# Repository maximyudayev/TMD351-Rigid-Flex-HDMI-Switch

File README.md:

# Rigid-Flex HDMI Switch - TI TMDS351
This HDMI switch board was built as part of my Hardware Design course at KU Leuven - Campus GroupT in academic year 2020-2021, taught by the awesome Gorik :wink:

PCB front side:

PCB back side:

Mechanical layer details:

100 Ohm differential trace width:

All the design files are under GPL3 and can be freely used for personal projects where this device can be of use.

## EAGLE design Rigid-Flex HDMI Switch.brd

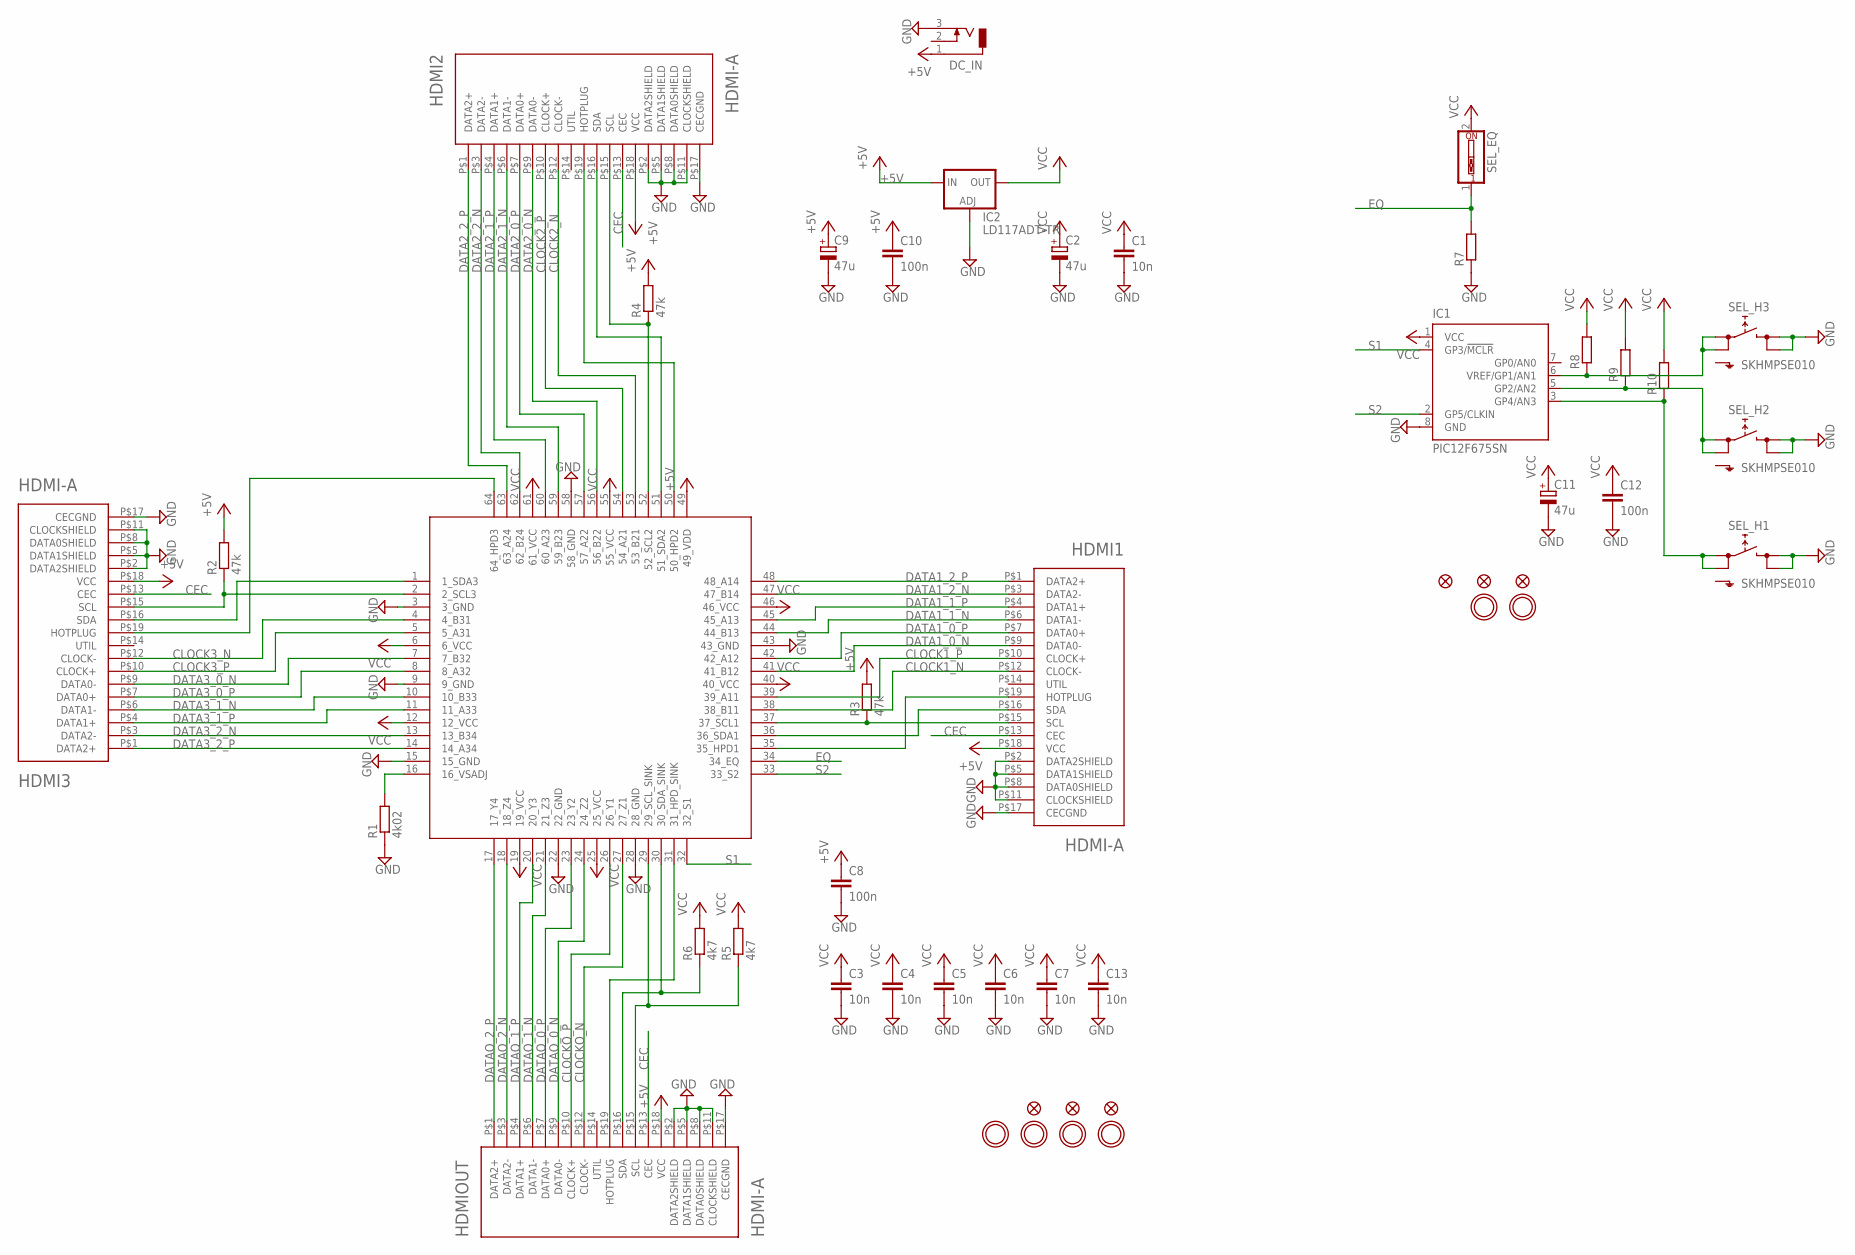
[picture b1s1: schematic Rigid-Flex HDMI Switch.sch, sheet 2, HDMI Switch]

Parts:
C1: 10n; C0402
C2, C9, C11: 47u; SMC_A
C3, C4, C5, C6, C7, C13: 10n; 0402
C8: 100n; 0402
C10, C12: 100n; C0402
DC_IN: DCJ0303
FID1, FID2, FID3, FID4, FID5, FID6: FIDUCIAL""; FIDUCIAL_1MM
HDMI1, HDMI2, HDMI3: HDMI-A; HDMI_A
HDMIOUT: HDMI-A; HDMI_A
IC1: PIC12F675SN; SO-08
IC2: LD117ADT-TR; DPACK
R1: 4k02; 0402
R2, R3, R4: 47k; 0402
R5, R6: 4k7; 0402
R7, R8, R9, R10: R-EU_R0805; R0805
SEL_EQ: SW_DIP-1; EDG-01
SEL_H1, SEL_H2, SEL_H3: SKHMPSE010; SKHMPXE010
U1: TMDS351TQFP64; QFP50P1200X1200X120-64
U$1, U$2, U$31, U$32, U$33, U$34: MOUNTINGHOLE3.0; MOUNTINGHOLE_3.0_PLATED

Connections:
+5V: C8.1, C9.+, C10.1, DC_IN.1, HDMI1.P$18 (VCC), HDMI2.P$18 (VCC), HDMI3.P$18 (VCC), HDMIOUT.P$18 (VCC), IC2.3 (IN), R2.2, R3.2, R4.2, U1.49 (49_VDD)
CEC: HDMI1.P$13 (CEC), HDMI2.P$13 (CEC), HDMI3.P$13 (CEC), HDMIOUT.P$13 (CEC)
CLOCK1_N: HDMI1.P$12 (CLOCK-), U1.38 (38_B11)
CLOCK1_P: HDMI1.P$10 (CLOCK+), U1.39 (39_A11)
CLOCK2_N: HDMI2.P$12 (CLOCK-), U1.53 (53_B21)
CLOCK2_P: HDMI2.P$10 (CLOCK+), U1.54 (54_A21)
CLOCK3_N: HDMI3.P$12 (CLOCK-), U1.4 (4_B31)
CLOCK3_P: HDMI3.P$10 (CLOCK+), U1.5 (5_A31)
CLOCKO_N: HDMIOUT.P$12 (CLOCK-), U1.27 (27_Z1)
CLOCKO_P: HDMIOUT.P$10 (CLOCK+), U1.26 (26_Y1)
DATA1_0_N: HDMI1.P$9 (DATA0-), U1.41 (41_B12)
DATA1_0_P: HDMI1.P$7 (DATA0+), U1.42 (42_A12)
DATA1_1_N: HDMI1.P$6 (DATA1-), U1.44 (44_B13)
DATA1_1_P: HDMI1.P$4 (DATA1+), U1.45 (45_A13)
DATA1_2_N: HDMI1.P$3 (DATA2-), U1.47 (47_B14)
DATA1_2_P: HDMI1.P$1 (DATA2+), U1.48 (48_A14)
DATA2_0_N: HDMI2.P$9 (DATA0-), U1.56 (56_B22)
DATA2_0_P: HDMI2.P$7 (DATA0+), U1.57 (57_A22)
DATA2_1_N: HDMI2.P$6 (DATA1-), U1.59 (59_B23)
DATA2_1_P: HDMI2.P$4 (DATA1+), U1.60 (60_A23)
DATA2_2_N: HDMI2.P$3 (DATA2-), U1.62 (62_B24)
DATA2_2_P: HDMI2.P$1 (DATA2+), U1.63 (63_A24)
DATA3_0_N: HDMI3.P$9 (DATA0-), U1.7 (7_B32)
DATA3_0_P: HDMI3.P$7 (DATA0+), U1.8 (8_A32)
DATA3_1_N: HDMI3.P$6 (DATA1-), U1.10 (10_B33)
DATA3_1_P: HDMI3.P$4 (DATA1+), U1.11 (11_A33)
DATA3_2_N: HDMI3.P$3 (DATA2-), U1.13 (13_B34)
DATA3_2_P: HDMI3.P$1 (DATA2+), U1.14 (14_A34)
DATAO_0_N: HDMIOUT.P$9 (DATA0-), U1.24 (24_Z2)
DATAO_0_P: HDMIOUT.P$7 (DATA0+), U1.23 (23_Y2)
DATAO_1_N: HDMIOUT.P$6 (DATA1-), U1.21 (21_Z3)
DATAO_1_P: HDMIOUT.P$4 (DATA1+), U1.20 (20_Y3)
DATAO_2_N: HDMIOUT.P$3 (DATA2-), U1.18 (18_Z4)
DATAO_2_P: HDMIOUT.P$1 (DATA2+), U1.17 (17_Y4)
EQ: R7.2, SEL_EQ.1, U1.34 (34_EQ)
GND: C1.2, C2.-, C3.2, C4.2, C5.2, C6.2, C7.2, C8.2, C9.-, C10.2, C11.-, C12.2, C13.2, DC_IN.3, HDMI1.P$2 (DATA2SHIELD), HDMI1.P$5 (DATA1SHIELD), HDMI1.P$8 (DATA0SHIELD), HDMI1.P$11 (CLOCKSHIELD), HDMI1.P$17 (CECGND), HDMI2.P$2 (DATA2SHIELD), HDMI2.P$5 (DATA1SHIELD), HDMI2.P$8 (DATA0SHIELD), HDMI2.P$11 (CLOCKSHIELD), HDMI2.P$17 (CECGND), HDMI3.P$2 (DATA2SHIELD), HDMI3.P$5 (DATA1SHIELD), HDMI3.P$8 (DATA0SHIELD), HDMI3.P$11 (CLOCKSHIELD), HDMI3.P$17 (CECGND), HDMIOUT.P$2 (DATA2SHIELD), HDMIOUT.P$5 (DATA1SHIELD), HDMIOUT.P$8 (DATA0SHIELD), HDMIOUT.P$11 (CLOCKSHIELD), HDMIOUT.P$17 (CECGND), IC1.8 (GND), IC2.1 (ADJ), R1.1, R7.1, SEL_H1.3 (2.1), SEL_H1.4 (2.2), SEL_H2.3 (2.1), SEL_H2.4 (2.2), SEL_H3.3 (2.1), SEL_H3.4 (2.2), U1.3 (3_GND), U1.9 (9_GND), U1.15 (15_GND), U1.22 (22_GND), U1.28 (28_GND), U1.43 (43_GND), U1.58 (58_GND)
unnamed: HDMI3.P$19 (HOTPLUG), U1.64 (64_HPD3)
unnamed: HDMI2.P$19 (HOTPLUG), U1.50 (50_HPD2)
unnamed: HDMI1.P$19 (HOTPLUG), U1.35 (35_HPD1)
unnamed: HDMIOUT.P$19 (HOTPLUG), U1.31 (31_HPD_SINK)
unnamed: HDMI3.P$16 (SDA), U1.1 (1_SDA3)
unnamed: HDMI3.P$15 (SCL), R2.1, U1.2 (2_SCL3)
unnamed: HDMI2.P$16 (SDA), U1.51 (51_SDA2)
unnamed: HDMI2.P$15 (SCL), R4.1, U1.52 (52_SCL2)
unnamed: HDMI1.P$15 (SCL), R3.1, U1.37 (37_SCL1)
unnamed: HDMI1.P$16 (SDA), U1.36 (36_SDA1)
unnamed: HDMIOUT.P$16 (SDA), R6.1, U1.30 (30_SDA_SINK)
unnamed: HDMIOUT.P$15 (SCL), R5.1, U1.29 (29_SCL_SINK)
unnamed: R1.2, U1.16 (16_VSADJ)
unnamed: IC1.6 (VREF/GP1/AN1), R8.1, SEL_H3.1 (1.1), SEL_H3.2 (1.2)
unnamed: IC1.5 (GP2/AN2), R9.1, SEL_H2.1 (1.1), SEL_H2.2 (1.2)
unnamed: IC1.3 (GP4/AN3), R10.1, SEL_H1.1 (1.1), SEL_H1.2 (1.2)
S1: IC1.4 (GP3/!MCLR), U1.32 (32_S1)
S2: IC1.2 (GP5/CLKIN), U1.33 (33_S2)
VCC: C1.1, C2.+, C3.1, C4.1, C5.1, C6.1, C7.1, C11.+, C12.1, C13.1, IC1.1 (VCC), IC2.4 (OUT), R5.2, R6.2, R8.2, R9.2, R10.2, SEL_EQ.2, U1.6 (6_VCC), U1.12 (12_VCC), U1.19 (19_VCC), U1.25 (25_VCC), U1.40 (40_VCC), U1.46 (46_VCC), U1.55 (55_VCC), U1.61 (61_VCC)

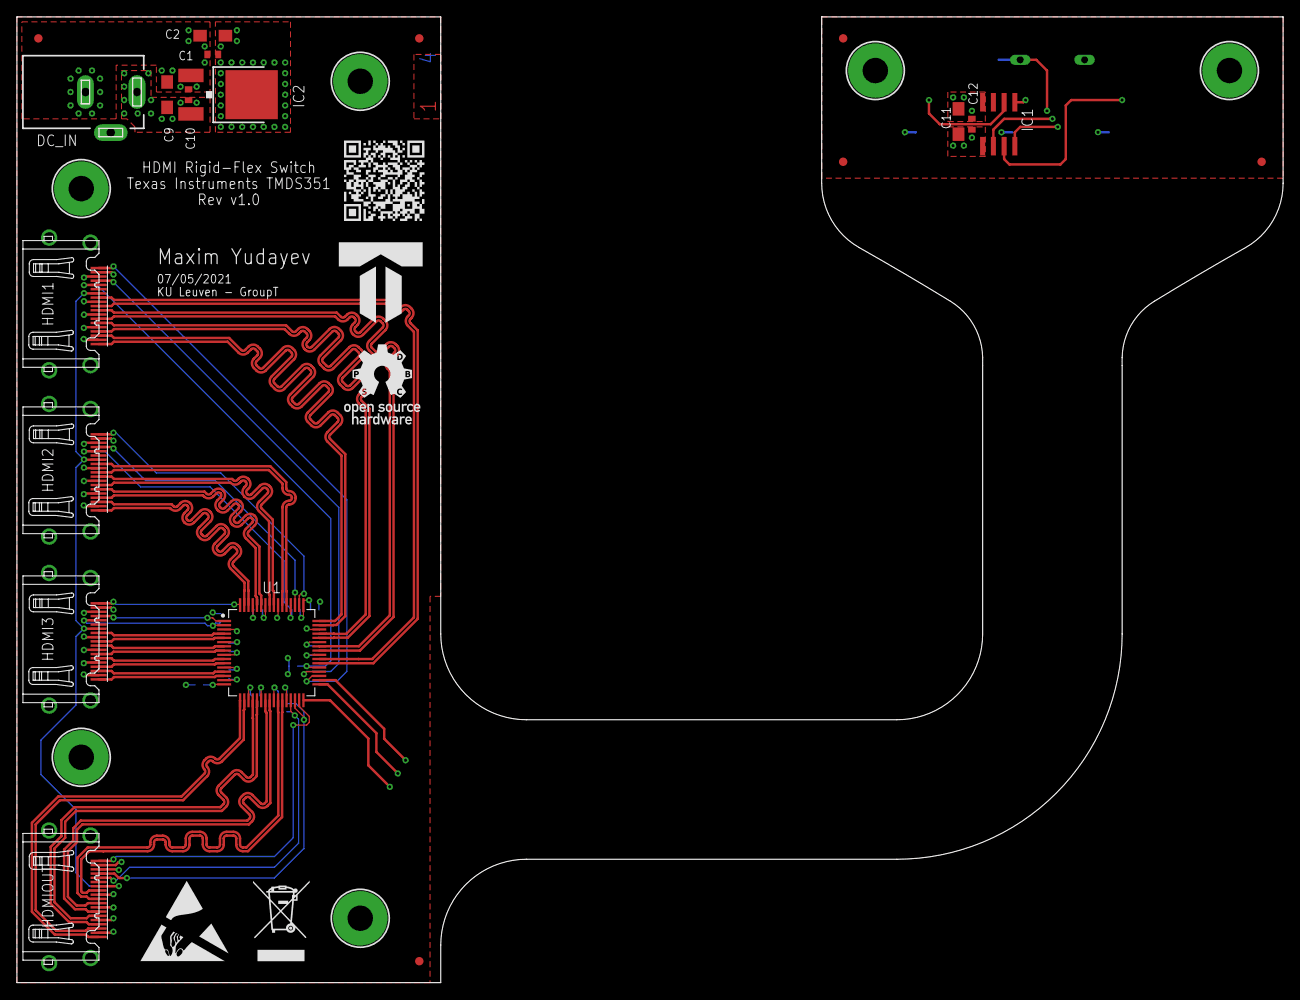
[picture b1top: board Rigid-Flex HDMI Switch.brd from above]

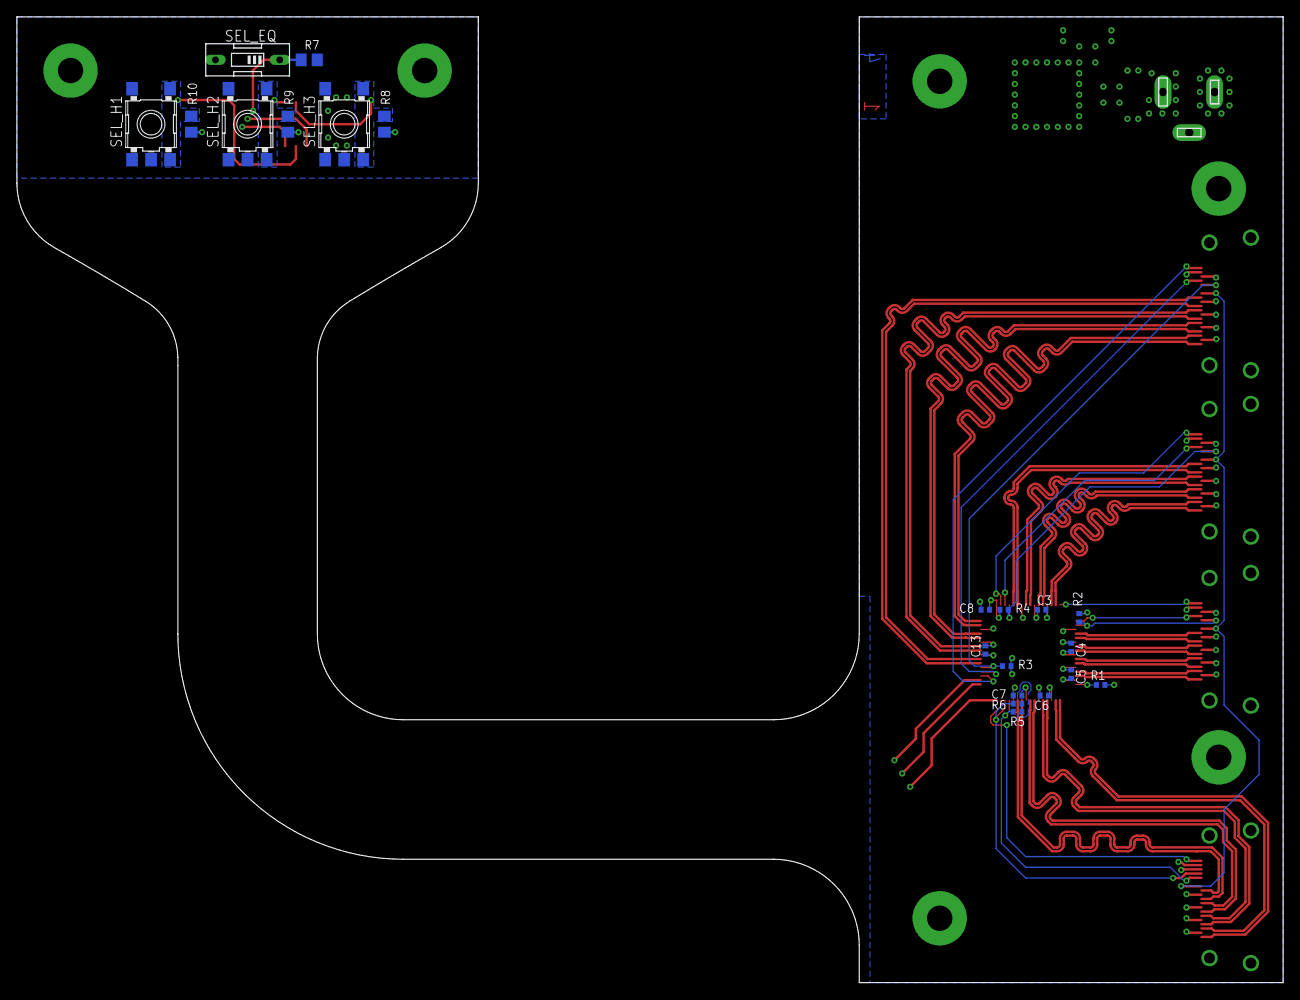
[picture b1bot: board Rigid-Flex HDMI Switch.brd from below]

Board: 4 copper layers, 149.9 x 114.3 mm, 47 parts (21 on the bottom side), 55 nets.

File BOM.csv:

"Qty";"Value";"Device";"Package";"Parts";"Description";"";
"1";"";"DCJ0303";"DCJ0303";"DC_IN";"DC POWER JACK";"";
"4";"";"R-EU_R0805";"R0805";"R7, R8, R9, R10";"RESISTOR, European symbol";"";
"1";"";"SW_DIP-1";"EDG-01";"SEL_EQ";"DIP SWITCH";"";
"2";"100n";"C-EUC0402";"C0402";"C10, C12";"CAPACITOR, European symbol";"";
"1";"100n";"C0402";"0402";"C8";"";"";
"1";"10n";"C-EUC0402";"C0402";"C1";"CAPACITOR, European symbol";"";
"6";"10n";"C0402";"0402";"C3, C4, C5, C6, C7, C13";"";"";
"3";"47k";"R0402";"0402";"R2, R3, R4";"";"";
"3";"47u";"CPOL-EUSMCA";"SMC_A";"C2, C9, C11";"POLARIZED CAPACITOR, European symbol";"";
"1";"4k02";"R0402";"0402";"R1";"";"";
"2";"4k7";"R0402";"0402";"R5, R6";"";"";
"6";"FIDUCIAL""";"FIDUCIAL""";"FIDUCIAL_1MM";"FID1, FID2, FID3, FID4, FID5, FID6";"Fiducial Alignment Points";"";
"4";"HDMI-A";"HDMI-A";"HDMI_A";"HDMI1, HDMI2, HDMI3, HDMIOUT";"Horizonal HDMI type "A" jack";"";
"1";"LD117ADT-TR";"LD117ADT-TR";"DPACK";"IC2";"Low drop fixed and adjustable positive voltage regulators 1 A";"";
"6";"MOUNTINGHOLE3.0";"MOUNTINGHOLE3.0";"MOUNTINGHOLE_3.0_PLATED";"U$1, U$2, U$31, U$32, U$33, U$34";"Mounting Hole";"";
"1";"PIC12F675SN";"PIC12F675SN";"SO-08";"IC1";"8-Pin FLASH-Based 8-Bit CMOS Microcontroller";"";
"3";"SKHMPSE010";"SKHMPSE010";"SKHMPXE010";"SEL_H1, SEL_H2, SEL_H3";"6.2 X 6.5mm TACT Switch (SMD)";"";
"1";"TMDS351TQFP64";"TMDS351TQFP64";"QFP50P1200X1200X120-64";"U1";"";"";

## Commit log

2021-05-06 Full PCB design, images, BOM, misc
2021-05-07 Added gerbers, rigid-flex outline, CAM and images
    +: Custom CAM job file for WE 1Ri-2F-1Ri buildup to accomodate
    separate rigid and flex outlines
    +: Updated images and README to display most recent information

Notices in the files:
parts and their libraries:
microbuilder: This work is placed in the public domain, and may be freely used for commercial and non-commercial work with the following conditions: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
